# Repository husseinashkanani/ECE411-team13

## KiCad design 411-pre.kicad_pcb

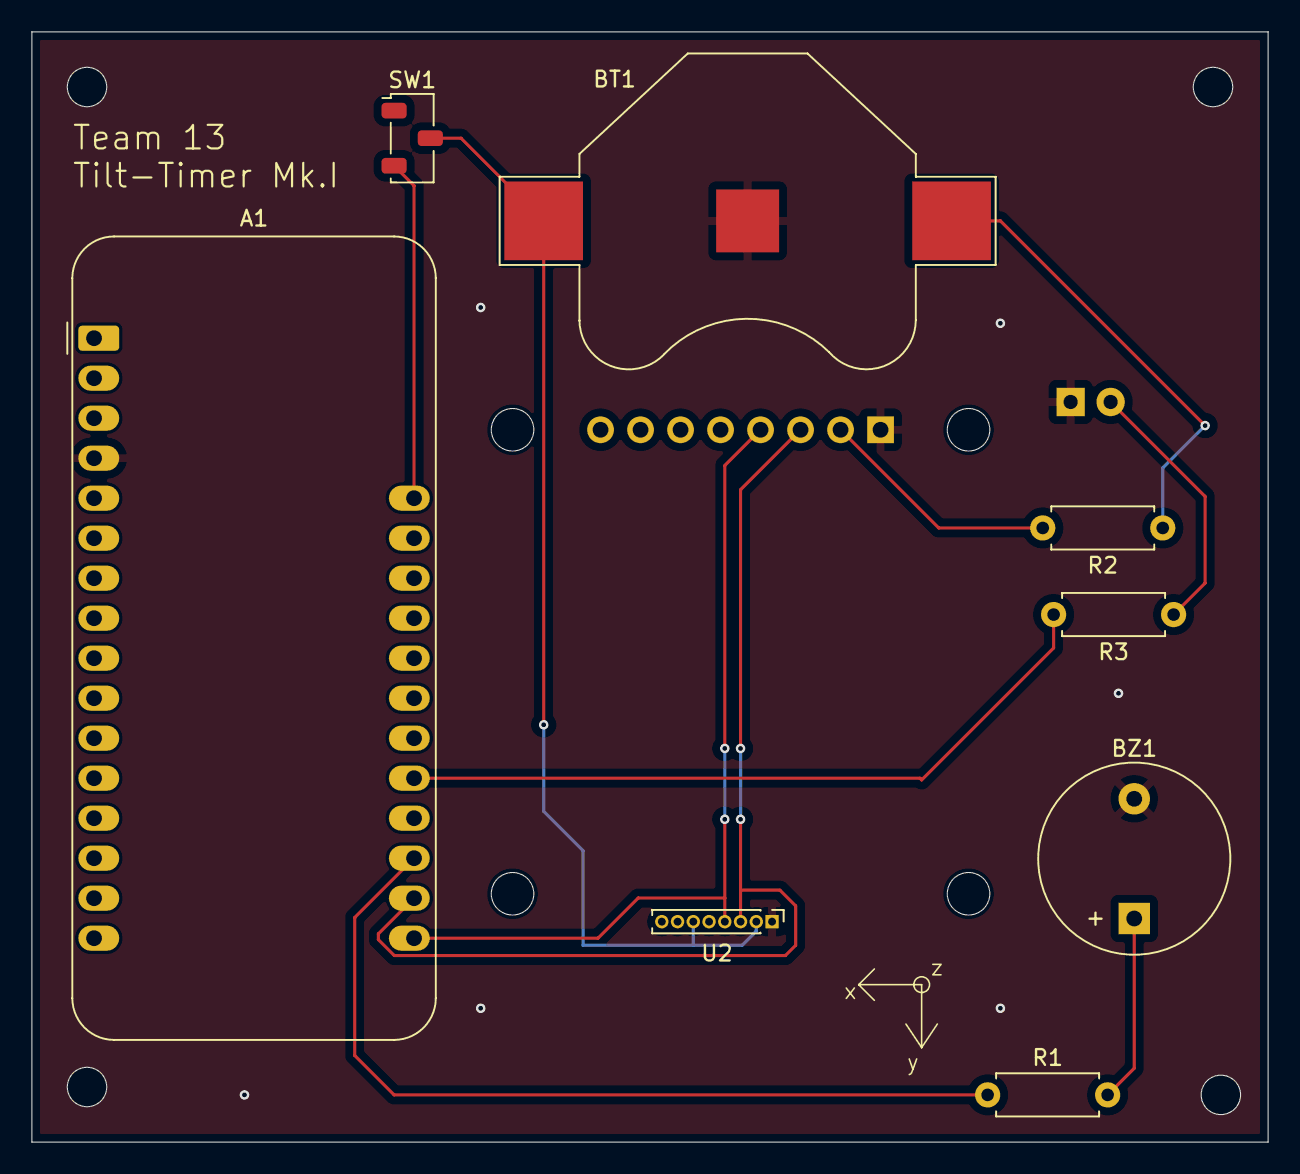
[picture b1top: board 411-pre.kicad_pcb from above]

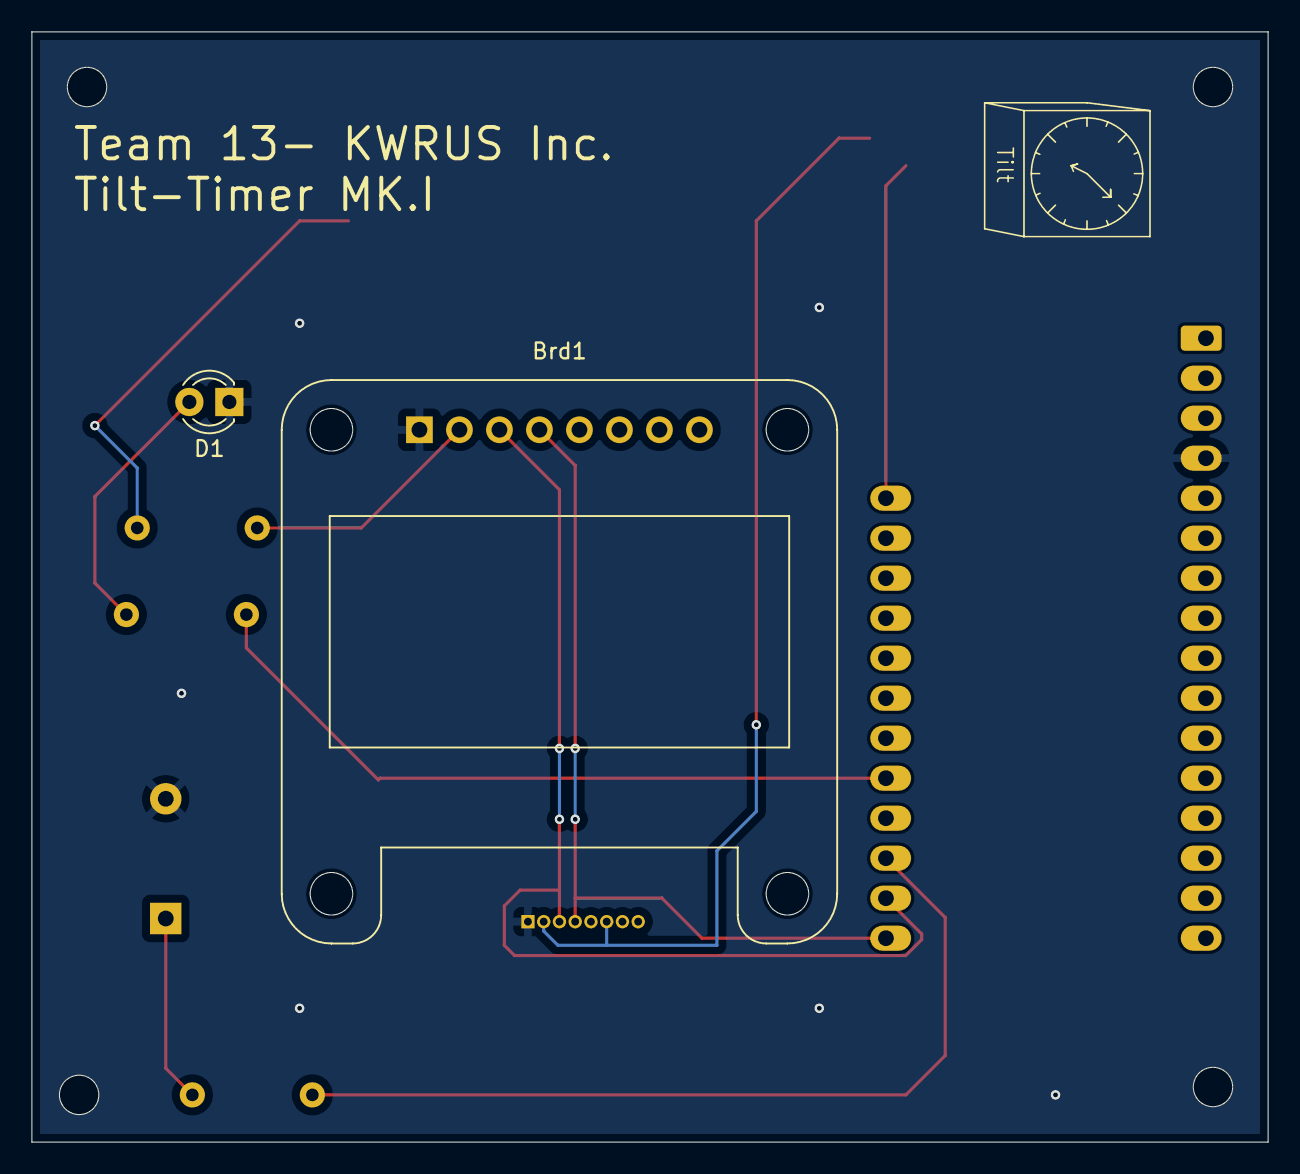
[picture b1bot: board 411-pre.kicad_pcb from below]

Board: 2 copper layers, 78.5 x 70.5 mm, 10 parts (2 on the bottom side), 10 nets.

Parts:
A1: Adafruit_Feather_HUZZAH32_ESP32; Adafruit_Feather
BT1: CR2032; BatteryHolder_Multicomp_BC-2001_1x2032
BZ1: Buzzer; Buzzer_12x9.5RM7.6
Brd1: SSD1306; Adafruit_SSD1306
D1: LED; LED_D3.0mm_FlatTop
R1, R3: 220; R_Axial_DIN0207_L6.3mm_D2.5mm_P7.62mm_Horizontal
R2: 4.7k; R_Axial_DIN0207_L6.3mm_D2.5mm_P7.62mm_Horizontal
SW1: SW_Nidec_CAS-120A1; Nidec_Copal_CAS-120A
U2: LIS3DH; PinHeader_1x08_P1.00mm_Vertical

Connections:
+BATT: BT1.1 (+), R2.1, SW1.2 (B), U2.2 (NC), U2.6 (SDI)
GND: A1.4 (GND), BT1.2 (-), BZ1.2 (-), Brd1.1 (GND), D1.1 (K), U2.1 (VDD_IO), U2.5 (GND)
unnamed: A1.19 (A6/IO14), R1.1
unnamed: A1.21 (A8/IO15), R3.2
unnamed: A1.18 (SCL/IO22), Brd1.3 (SCL), U2.3 (NC)
unnamed: A1.17 (SDA/IO23), Brd1.4 (SDA), U2.4 (SPC)
unnamed: A1.28 (VBAT), SW1.3 (A)
unnamed: BZ1.1 (+), R1.2
unnamed: Brd1.2 (VCC), R2.2
unnamed: D1.2 (A), R3.1

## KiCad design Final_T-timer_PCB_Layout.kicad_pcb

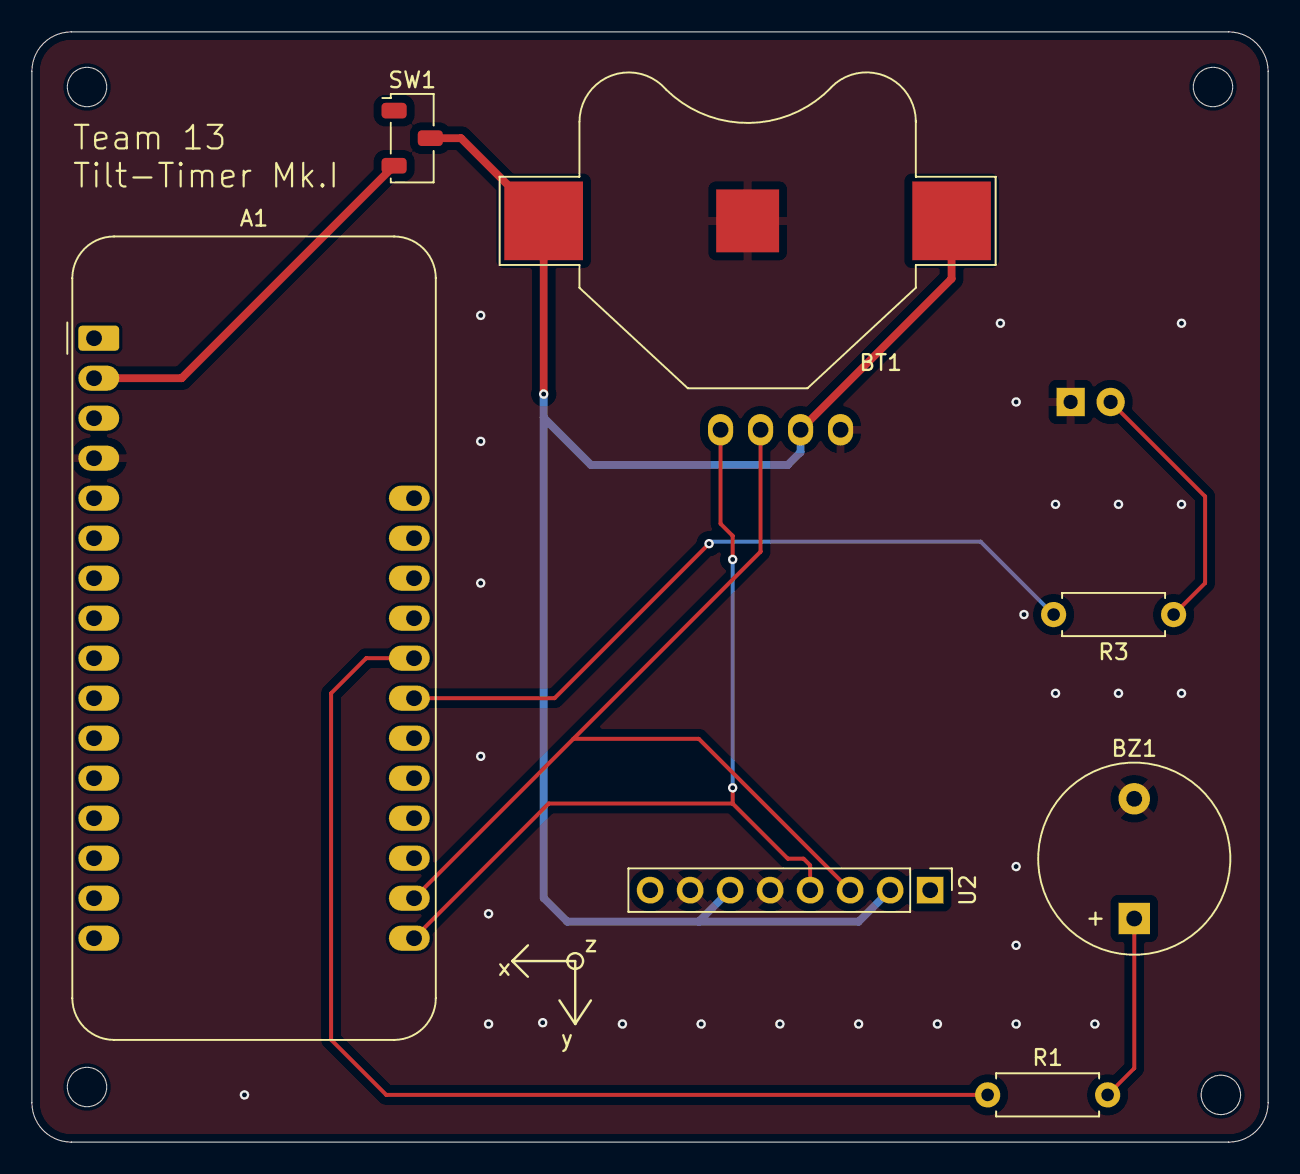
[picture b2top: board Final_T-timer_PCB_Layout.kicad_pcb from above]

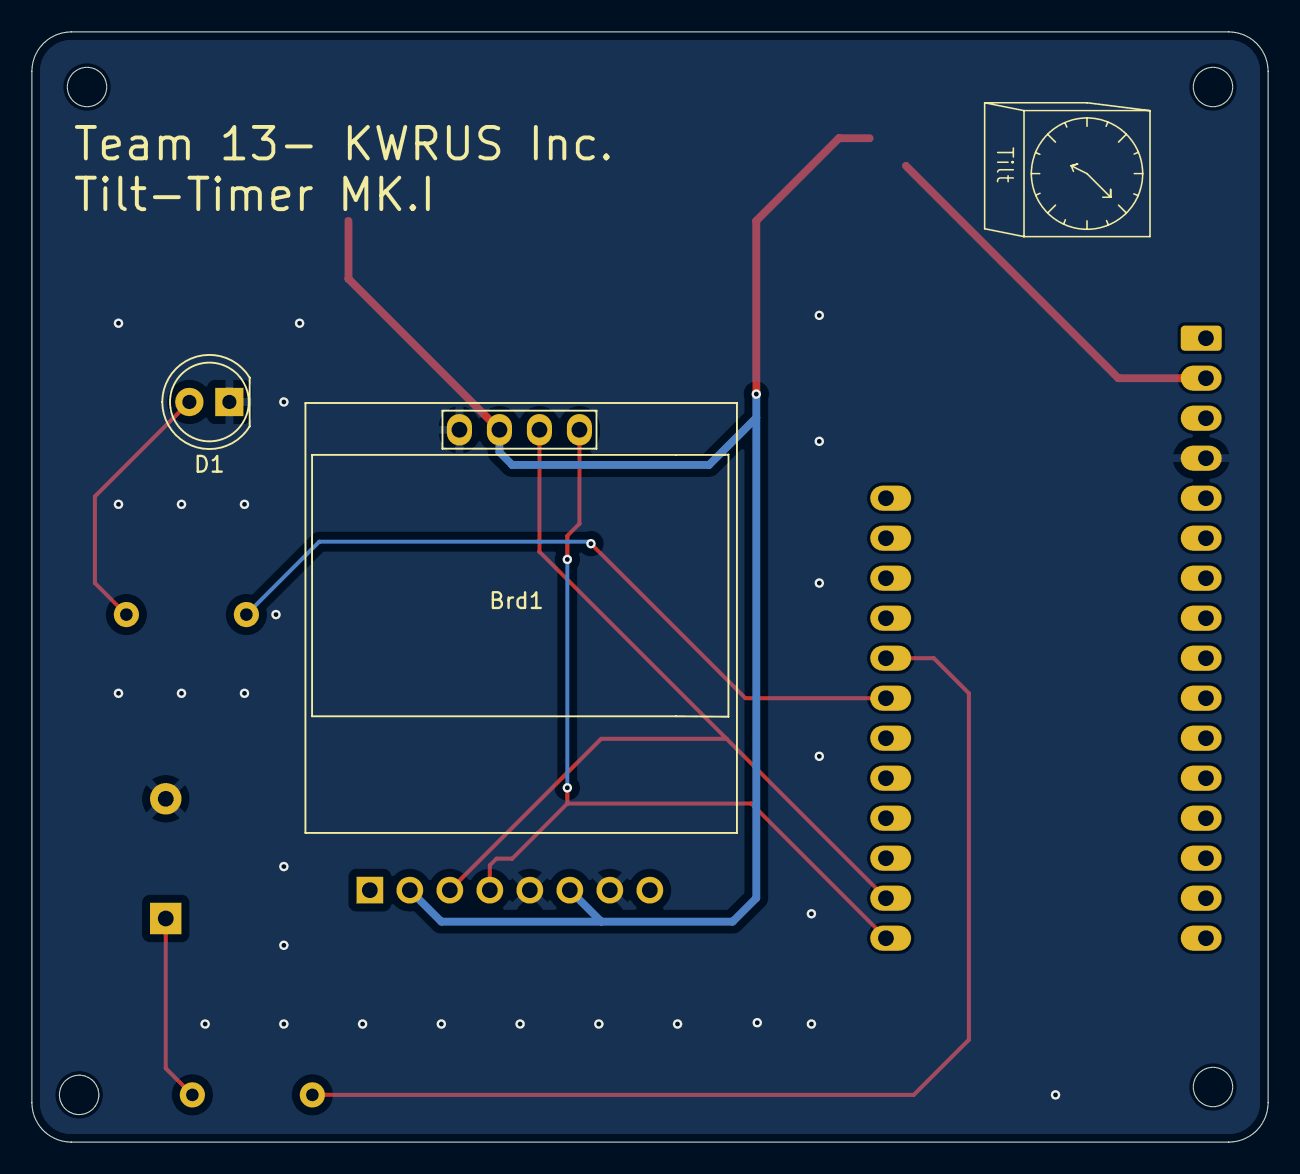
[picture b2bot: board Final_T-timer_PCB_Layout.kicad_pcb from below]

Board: 2 copper layers, 78.5 x 70.5 mm, 9 parts (2 on the bottom side), 9 nets.

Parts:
A1: Adafruit_Feather_HUZZAH32_ESP32; Adafruit_Feather
BT1: CR2032; BatteryHolder_Multicomp_BC-2001_1x2032
BZ1: Buzzer; Buzzer_12x9.5RM7.6
Brd1: SSD1306; 128x64OLED
D1: LED; LED_D5.0mm
R1, R3: 150; R_Axial_DIN0207_L6.3mm_D2.5mm_P7.62mm_Horizontal
SW1: SW_Nidec_CAS-120A1; Nidec_Copal_CAS-120A
U2: LIS3DH; PinHeader_1x08_P2.54mm_Vertical

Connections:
+BATT: BT1.1 (+), Brd1.2 (VCC), SW1.2 (B), U2.8 (CS)
GND: A1.4 (GND), BT1.2 (-), BZ1.2 (-), Brd1.1 (GND), D1.1 (K), U2.5 (GND), U2.7 (SDO)
unnamed: A1.2 (3V3), SW1.3 (A)
unnamed: A1.23 (A10/IO27), R3.2
unnamed: A1.24 (A11/IO12), R1.1
unnamed: A1.18 (SCL/IO22), Brd1.3 (SCL), U2.4 (SPC)
unnamed: A1.17 (SDA/IO23), Brd1.4 (SDA), U2.6 (SDI)
unnamed: BZ1.1 (+), R1.2
unnamed: D1.2 (A), R3.1

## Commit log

2025-11-19 Add files via upload (#3)
2025-12-12 Add Tilt Timer functionality with OLED display code
